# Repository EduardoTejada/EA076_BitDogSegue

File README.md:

# BitDogSegue

## Sobre o projeto
O BitDogSegue é um robô seguidor de linha usando a placa BitDogLab como base e é fruto dos esforços realizados na disciplina EA076 - Laboratório de Sistemas Embarcados, ministrada na Unicamp pelo professor Fabiano Fruett. Desenvolvido pelos alunos Eduardo Pereira e José Braga, esse robô foi desenvolvido visando aprimorar os conhecimentos em eletrônica e programação (_hardware_ e _software) de estudantes e entusiastas nessa área.

Para mais detalhes sobre o projeto, acesse a documentação.

[Documentação](https://docs.google.com/document/d/1uC-1uOnyaNJ6YEM8gG9vPqVe9gIrEa1YJPF4Q7OL9hc/edit?usp=sharing)
[Apresentação](https://theresistance.my.canva.site/bitdogsegue)

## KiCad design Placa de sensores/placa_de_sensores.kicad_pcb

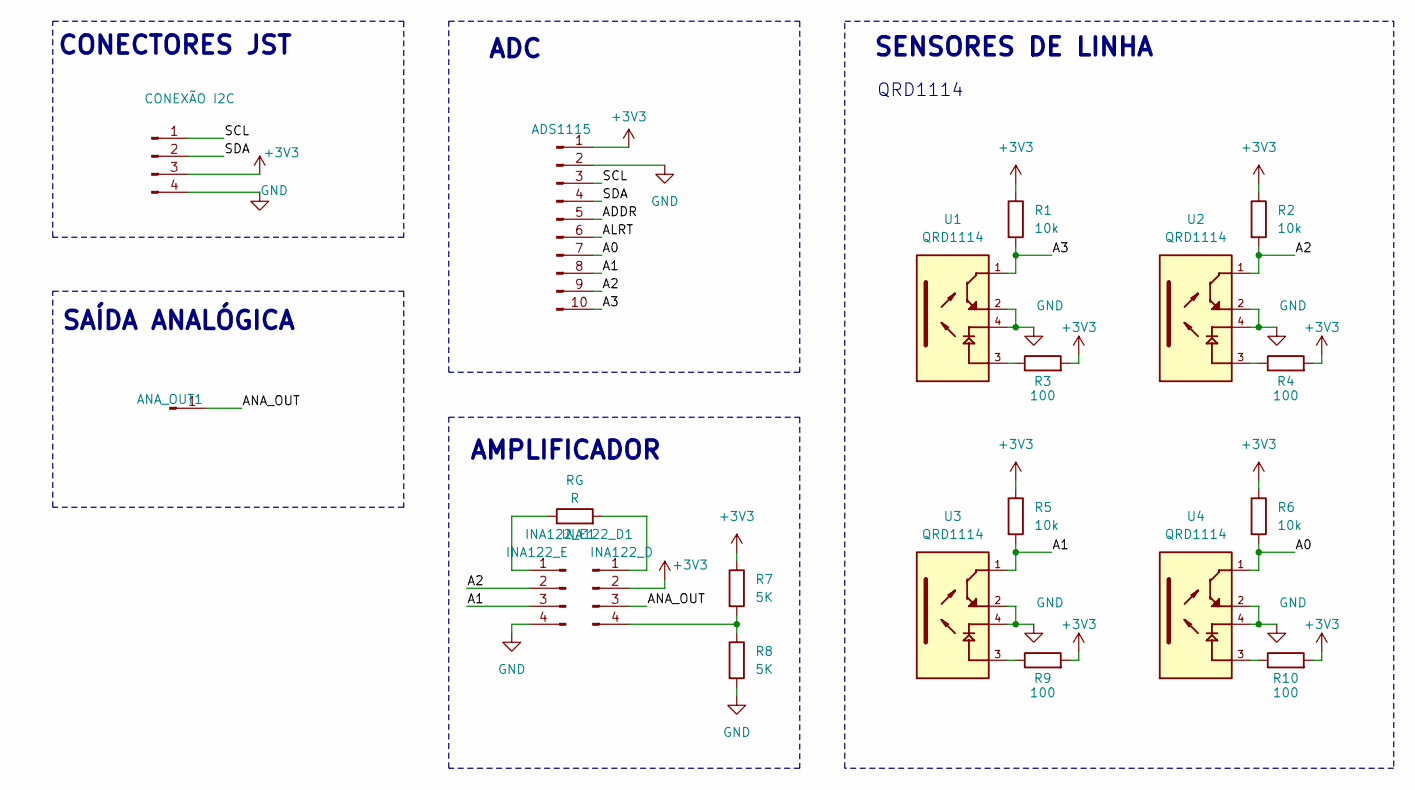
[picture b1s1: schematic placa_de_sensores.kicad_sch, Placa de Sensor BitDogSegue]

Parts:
ADS1115: ADS1115; PinHeader_1x10_P2.54mm_Vertical
ANA_OUT1: PinHeader_1x01_P1.00mm_Vertical
CONEXÃO-I2C1: CONEXÃO I2C; JST_EH_B4B-EH-A_1x04_P2.50mm_Vertical
INA122_D1: INA122_D; PinHeader_1x04_P2.54mm_Vertical
INA122_E1: INA122_E; PinHeader_1x04_P2.54mm_Vertical
R1, R2, R5, R6: 10k; R_Axial_DIN0207_L6.3mm_D2.5mm_P7.62mm_Horizontal
R3, R4, R9, R10: 100; R_Axial_DIN0207_L6.3mm_D2.5mm_P7.62mm_Horizontal
R7, R8: 5K; R_Axial_DIN0207_L6.3mm_D2.5mm_P7.62mm_Horizontal
RG: R; R_Axial_DIN0207_L6.3mm_D2.5mm_P7.62mm_Horizontal
U1, U2, U3, U4: QRD1114; ONS_QRD1114; PARTREV 1.3.0; DIGI-KEY_PART_NUMBER QRD1114-ND

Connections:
+3V3: ADS1115.1, CONEXÃO-I2C1.3, INA122_D1.2, R1.1, R2.1, R3.2, R4.2, R5.1, R6.1, R7.1, R9.2, R10.2; also elsewhere on the board
/A0: ADS1115.7, R6.2, U4.1
/A1: ADS1115.8, INA122_E1.3, R5.2, U3.1
/A2: ADS1115.9, INA122_E1.2, R2.2, U2.1
/A3: ADS1115.10, R1.2, U1.1
/ADDR: ADS1115.5
/ALRT: ADS1115.6
/SCL: ADS1115.3, CONEXÃO-I2C1.1
/SDA: ADS1115.4, CONEXÃO-I2C1.2
GND: ADS1115.2, CONEXÃO-I2C1.4, INA122_E1.4, R8.2, U1.2, U1.4, U2.2, U2.4, U3.2, U3.4, U4.2, U4.4
unnamed: ANA_OUT1.1, INA122_D1.3
unnamed 12: INA122_D1.1, RG.2; also elsewhere on the board
unnamed 13: INA122_D1.4, R7.2, R8.1; also elsewhere on the board
unnamed: INA122_E1.1, RG.1
unnamed: R3.1, U1.3
unnamed: R4.1, U2.3
unnamed: R9.1, U3.3
unnamed: R10.1, U4.3

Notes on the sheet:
ADC
SAÍDA ANALÓGICA
SENSORES DE LINHA
QRD1114
CONECTORES JST
AMPLIFICADOR

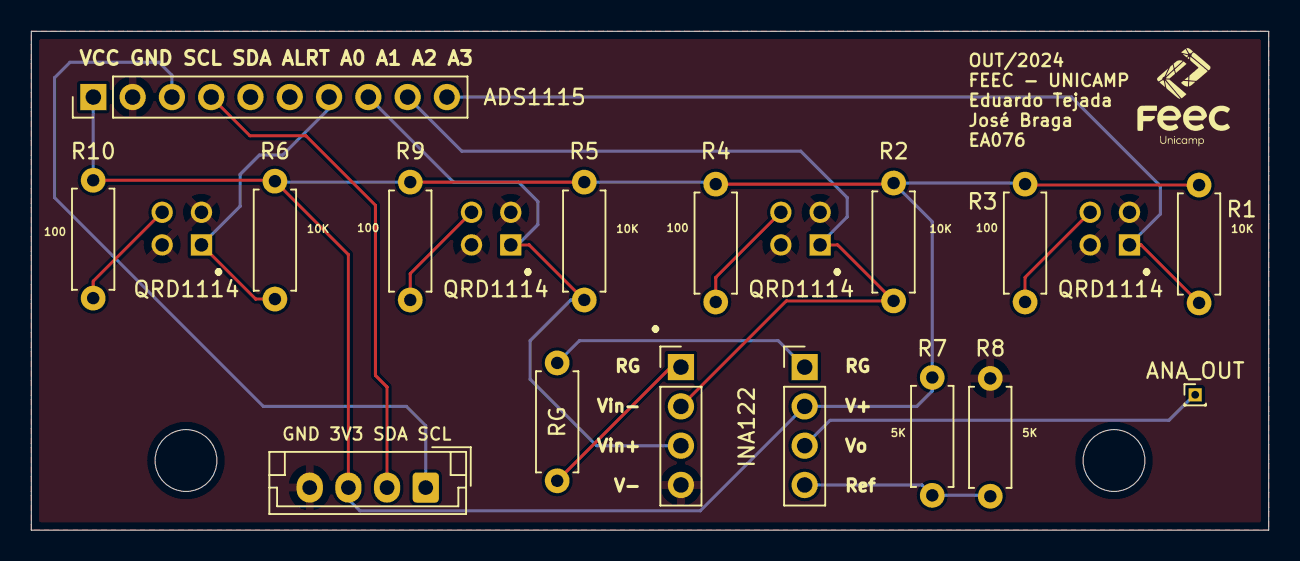
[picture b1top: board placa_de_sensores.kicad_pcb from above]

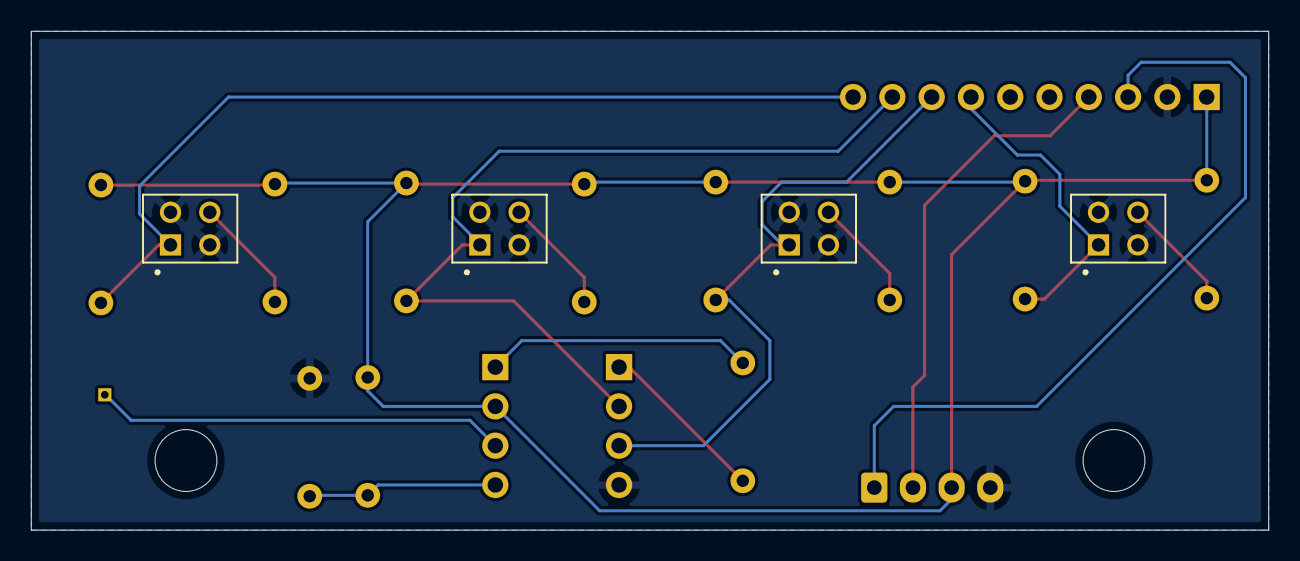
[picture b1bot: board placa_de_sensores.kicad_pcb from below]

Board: 2 copper layers, 80.0 x 32.2 mm, 20 parts (4 on the bottom side), 16 nets.

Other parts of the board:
ANA_OUT: PinHeader_1x01_P1.00mm_Vertical
INA122: INA122_D; PinHeader_1x04_P2.54mm_Vertical

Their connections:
+3V3: INA122.2; also elsewhere on the board
/ANA_OUT: ANA_OUT.1, INA122.3
unnamed 12: INA122.1; also elsewhere on the board
unnamed 13: INA122.4; also elsewhere on the board

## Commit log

2024-11-30 melhorias nos comentários, remoção de função não utilizadas
2024-11-30 Organizando arquivos
2024-11-30 Update README.md
    Descrição do projeto e link para o relatório
2024-11-30 Update README.md
    Correção de gramática
